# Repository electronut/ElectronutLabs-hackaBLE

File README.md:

> **Note**: This repository has been moved to our GitLab page on May 2019, and will not receive any updates or be monitored. Please follow this link to go to the new repository: https://gitlab.com/electronutlabs-public/ElectronutLabs-HackaBLE

## What is hackaBLE ?

**hackaBLE** is a tiny (~ 18 mm x 28 mm) Open Source Nordic nRF52832 based BLE development board you can embed in your BLE projects. It's designed such that you can use it in three ways:

- On a breadboard
- On a custom PCB, hand-soldered easily using the castellated 2.54 mm pitch headers
- On a custom PCB, using a stencil and oven, making use of extra pads underneath the PCB

hackaBLE uses offers more value than just using the BLE module directly - since it incorporates the necessary passive components - including the ones for the buck converter for power saving - and adds an RGB LED and a button for convenience. It's also much easier to solder than the bare modules. 

**Features**

- Raytac MDBT42 based on Nordic Semiconductor's nRF52832 SOC with chip antenna
- RGB LED
- Button user configurable, set as RESET by default
- SWD programming headers
- MCP1702 3.3 V LDO
- Reverse current protection.

Currently, there are two versions available in the market. Select your version of hackaBLE from below and follow the documentation. 

<h3><a href="#hackaBLE_v0.3">hackaBLE v0.3</a></h3>

<h3><a href="#hackaBLE_v2.2">hackaBLE v2.2</a></h3>

<h2 id="hackaBLE_v0.3"></h2>

## hackaBLE v0.3

This is the latest version of hackaBLE it uses **Raytac's nRF52832 module** by Nordic Semiconductors. This version uses MCP1702, a 3.3 V voltage and protection diode at the input which enables hackaBLE to consume very low current and also provides reverse current protection. It also comes with an RGB LED, user reset button and SWD programming headers.  

### hackaBLE v0.3 pinout

### hackaBLE v0.3 PCB Footprint

### hackaBLE v0.3 Schematic and Datasheet

- [schematic](pcb/ver0.3/hackaBLE_Schematic.pdf)
- datasheet

<hr>
<h2 id="hackaBLE_v2.2"></h2>

## hackaBLE v2.2

hackaBLE v2.2 is a redesigned hackaBLE that used the BLE SoC directly rather than a module. This version of hackaBLE also comes with an RGB LED, button, and SWD programming headers. It has onboard BLE antenna. 

**[CAUTION]** hackaBLE v2.2 does not come with a regulator since it's designed for low power applications. MAX input to VDD is 3.6 V.

### hackaBLE v2.2 pinout

### Schematic for hackaBLE v2.2

- [Schematic](pcb/ver2.2/hackaBLE.pdf)

## Programming hackaBLE

hackaBLE uses the Nordic nRF52832 which in turn is based on an ARM Cortex-M4 core. So you can really program it with any ARM compatible programmer. We do have a convenient solution though, in the form of our [Bumpy][3] Blackmagic probe compatible SWD debugger and our [PogoProg][4].

As shown above, use the four SWD pins of PogoProg on hackaBLE to upload or debug hackaBLE.

Please [read the bumpy documentation][3] on using Bumpy to program hackaBLE.

For more details on nRF52 programming, please read our guide on [getting started with Nordic nRF5 SDK][1]. 

### Program using Arduino IDE

hackable does not ship with a bootloader, but it is supported in Arduino. Please visit [here](https://github.com/electronut/ElectronutLabs-bluey#Arduino) for details (but select Hackable in the board's menu).

[Here's](https://electronut.in/using-hackable-with-arduino/) a blog article which will help you create a BLE custom characteristic and program it to hackaBLE using Arduino IDE.

For more detailed programming guide go [here](https://docs.electronut.in/hackaBLE/programming_guide/)

## Soldering headers hackaBLE

hackaBLE can be used on a breadboard. Here's a video that shows how to solder headers on to hackaBLE.

## Buy a hackaBLE!

hackaBLE is available for purchase from our [Tindie store][2]. Please email us at **info@electronut.in** if you have any questions.

[1]: https://github.com/electronut/ElectronutLabs-bluey/blob/master/nrf5-sdk-setup.md
[2]: https://www.tindie.com/stores/ElectronutLabs/
[3]: https://gitlab.com/electronut/ElectronutLabs-Bumpy
[4]: https://gitlab.com/electronutlabs-public/ElectronutLabs-PogoProg

## Code Repository

You can find all code and design files related to HackaBLE in this [repository](https://gitlab.com/electronutlabs-public/ElectronutLabs-HackaBLE).

## About Electronut Labs

**Electronut Labs** is an Embedded Systems company based in Bangalore, India. More 
information at our [website](https://electronut.in).

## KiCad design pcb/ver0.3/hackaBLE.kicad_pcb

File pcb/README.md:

# BlueyCore
A compact Nordic nRF52832 BLE module for embedding in projects.

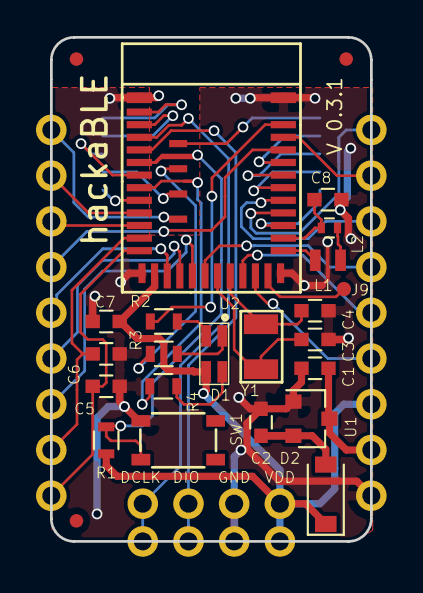
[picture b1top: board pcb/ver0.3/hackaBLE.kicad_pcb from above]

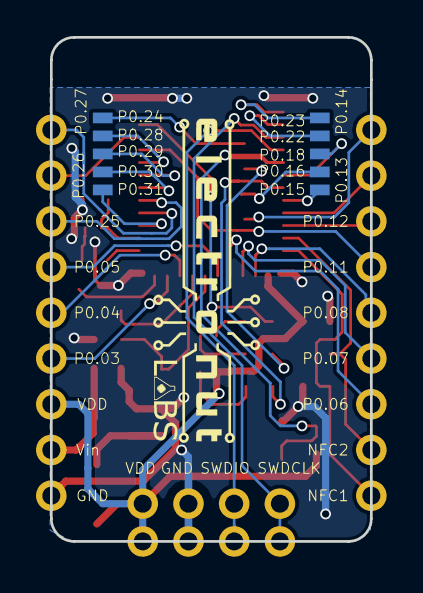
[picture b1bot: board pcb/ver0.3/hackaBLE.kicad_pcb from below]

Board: 2 copper layers, 17.8 x 28.0 mm, 29 parts (2 on the bottom side), 44 nets.

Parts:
C1, C2, C8: 1uF; C_0603
C3, C4: 12pF; C_0603
C5, C6: 300pF; C_0603
C7: 10uF; C_0603
D1: LED_ARGB; RGB_LED
D2: MBR130; D_SOD-123
J1: INPUT; Pin_Header_Straight_1x02_Pitch2.54
J2: NFC; Pin_Header_Straight_1x02_Pitch2.54
J3, J8: SWD; Pin_Header_Straight_1x04_Pitch2.54
J4, J6: GPIO; Pin_Header_Straight_1x07_Pitch2.54
J5, J7: GPIO; 5pin_header
J9: TEST_1P; test_point
L1: 10uH; Neosid_Inductor_SM0603CG
L2: 15nH; L_0402
R1: 10K; R_0603
R2: 200R; R_0603
R3, R4: 100R; R_0603
SW1: SW_Push; PTS810_Switch
U1: MCP1702; SOT-23
U2: MDBT42
Y1: 32.768KHz; ABS07_crystal

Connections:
BLUE: R4.2, U2.8
GND: C1.1, C2.1, C3.2, C4.2, C5.2, C6.1, C7.1, C8.2, J1.2, J3.3, J8.3, SW1.1, U1.1, U2.1, U2.14, U2.25, U2.37
GREEN: R3.2, U2.39
NFC1: C5.1, J2.1, U2.13
NFC2: C6.2, J2.2, U2.12
unnamed: C2.2, D2.2, U1.2
unnamed: C3.1, U2.20, Y1.1
unnamed: C4.1, U2.21, Y1.2
unnamed: C8.1, L2.1, U2.27
unnamed: D1.1, R3.1
unnamed: D1.2, R2.1
unnamed: D1.4, R4.1
unnamed: L1.1, L2.2
unnamed: L1.2, U2.26
P0.02: J9.1, U2.24
P0.03: J6.2, U2.23
P0.04: J6.3, U2.22
P0.05: J6.4, U2.19
P0.06: J4.1, U2.18
P0.07: J4.2, U2.17
P0.08: J4.3, U2.16
P0.11: J4.4, U2.34
P0.12: J4.5, U2.11
P0.13: J4.6, U2.10
P0.14: J4.7, U2.41
P0.15: J5.1, U2.9
P0.16: J5.2, U2.40
P0.18: J5.3, U2.7
P0.22: J5.4, U2.3
P0.23: J5.5, U2.2
P0.24: J7.1, U2.38
P0.25: J6.5, U2.30
P0.26: J6.6, U2.35
P0.27: J6.7, U2.29
P0.28: J7.2, U2.33
P0.29: J7.3, U2.32
P0.30: J7.4, U2.31
P0.31: J7.5, U2.28
RED: R2.2, U2.36
RESET: R1.2, SW1.2, U2.6
SWDCLK: J3.1, J8.1, U2.4
SWDIO: J3.2, J8.2, U2.5
VDD: C7.2, D1.3, D2.1, J3.4, J6.1, J8.4, R1.1, U2.15
Vin: C1.2, J1.1, U1.3

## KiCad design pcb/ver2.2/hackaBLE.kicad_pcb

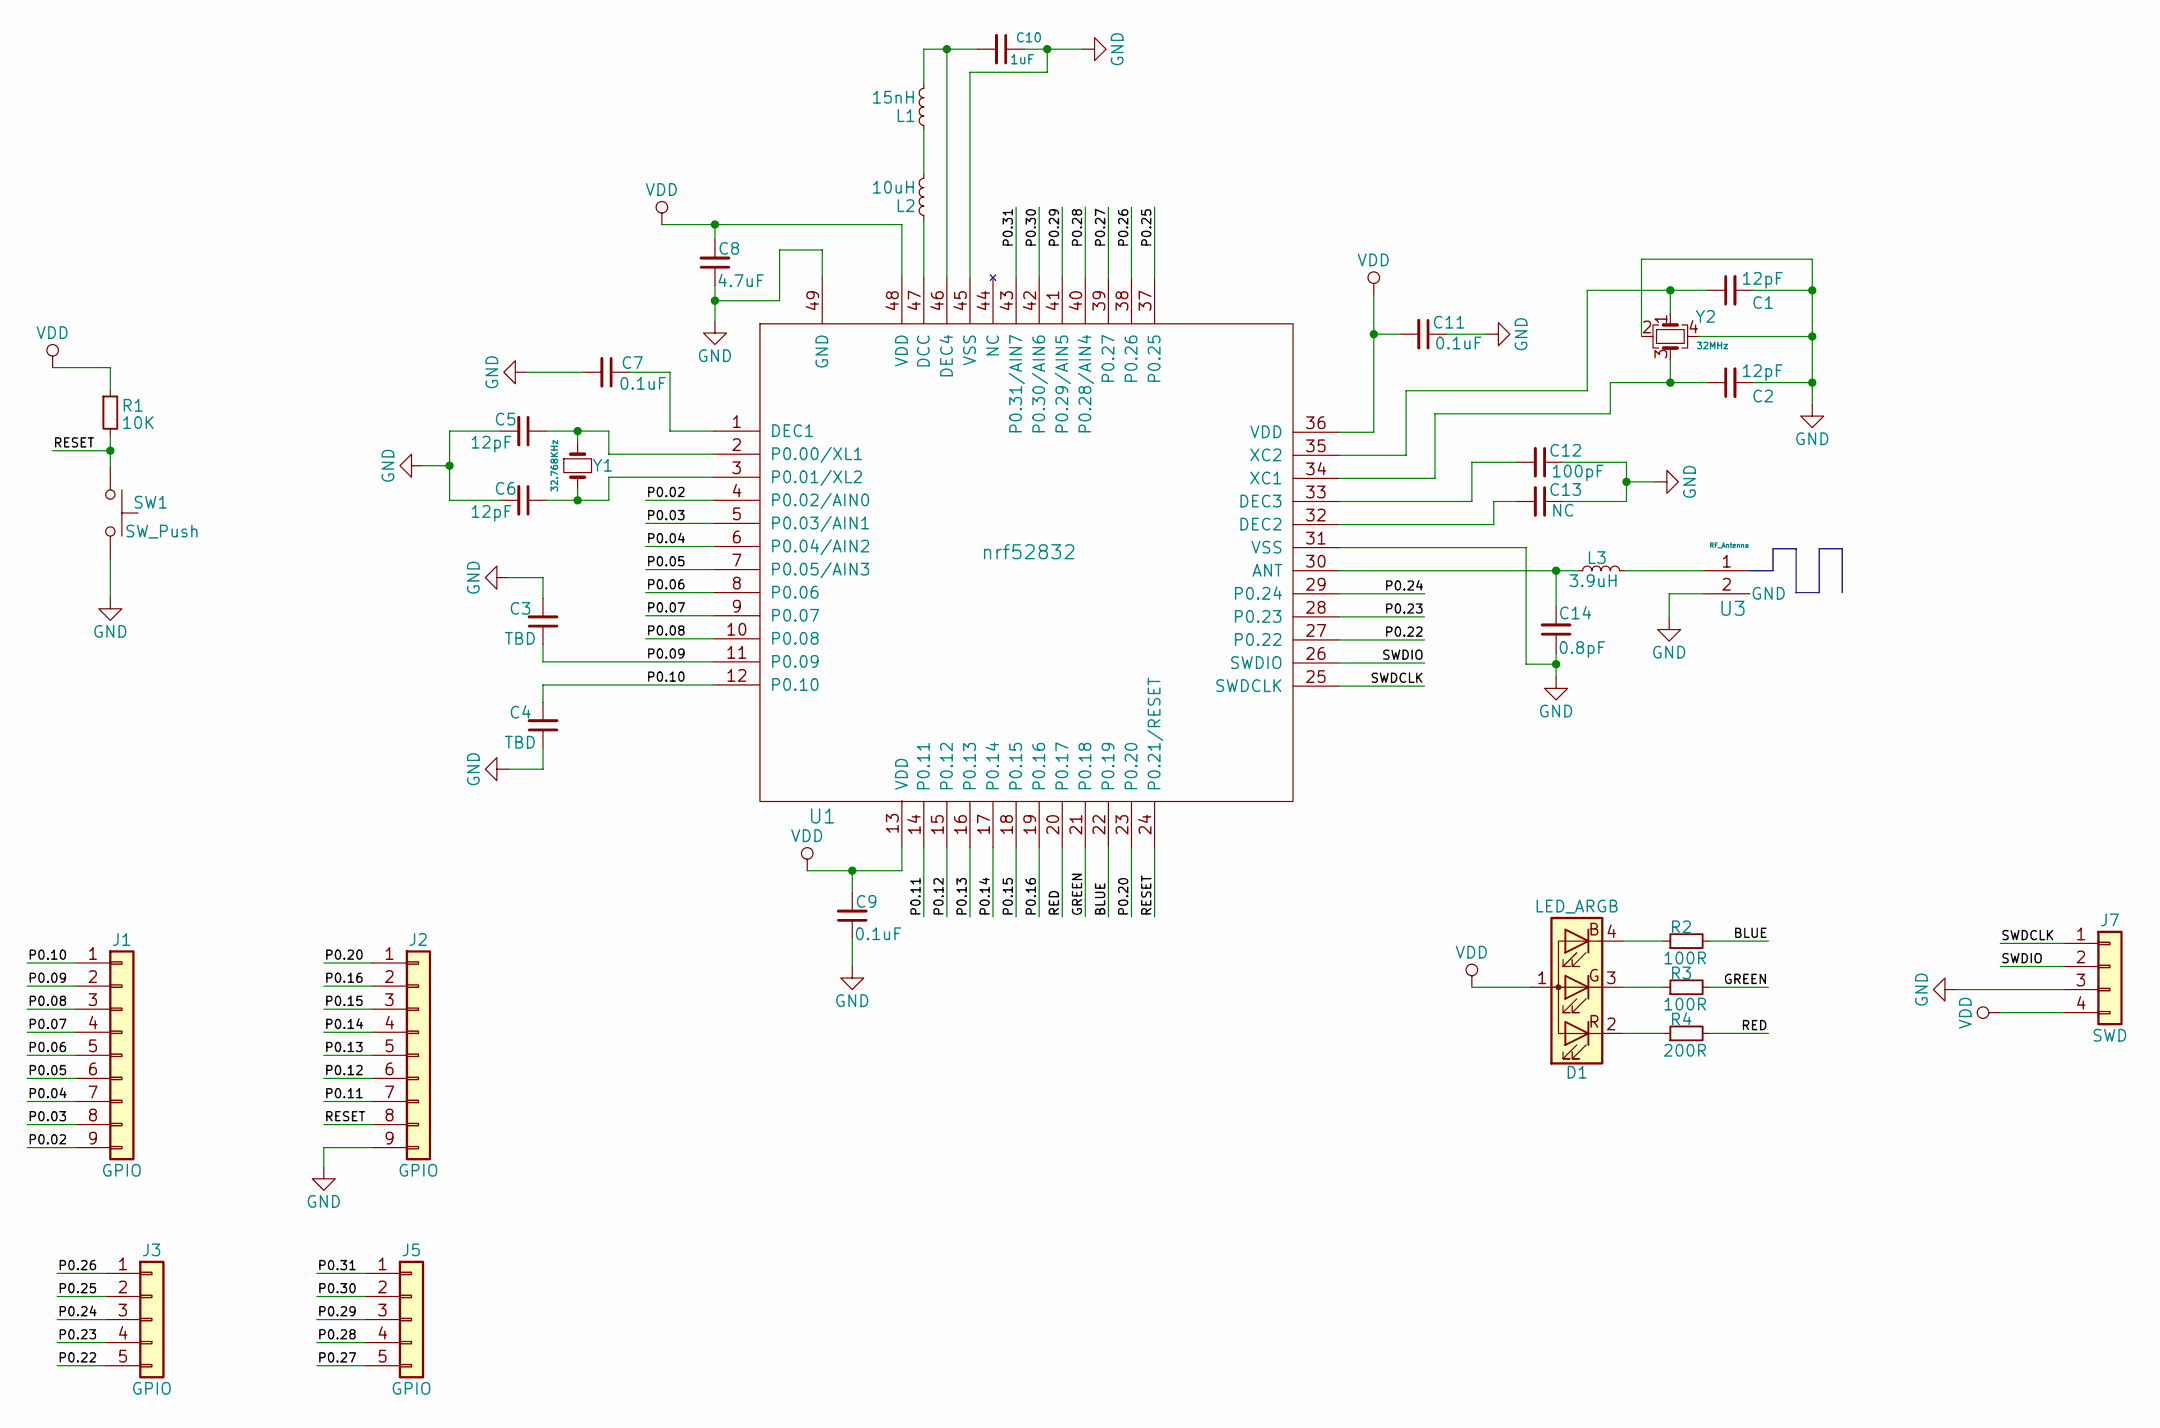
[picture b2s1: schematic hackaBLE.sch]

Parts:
C1, C2, C5, C6: 12pF; C_0402
C3, C4: TBD; C_0603
C7, C9, C11: 0.1uF; C_0402
C8: 4.7uF; C_0603
C10: 1uF; C_0603
C12: 100pF; C_0402
C13: NC; C_0402
C14: 0.8pF; SMD_0402
D1: LED_ARGB; RGB_LED
J1, J2: GPIO; PinHeaderStraight1x09_Pitch2.54mm
J3, J5: GPIO; 5pin_header
J7: SWD; Pin_Header_Straight_1x05_Pitch2.54mm
L1: 15nH; C_0402
L2: 10uH; Neosid_Inductor_SM0603CG
L3: 3.9uH; SMD_0402
R1: 10K; R_0603
R2, R3: 100R; R_0603
R4: 200R; R_0603
SW1: SW_Push; PTS810_Switch
U1: nrf52832; nRF52832
U3: RF_Antenna; Antenna-2.45GHZ_mirror
Y1: 32.768KHz; ABS07_crystal
Y2: 32MHz; 32MHz_crystal

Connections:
/BLUE: R2.2, U1.22 (P0.19)
/GREEN: R3.2, U1.21 (P0.18)
/P0.02: J1.9, U1.4 (P0.02/AIN0)
/P0.03: J1.8, U1.5 (P0.03/AIN1)
/P0.04: J1.7, U1.6 (P0.04/AIN2)
/P0.05: J1.6, U1.7 (P0.05/AIN3)
/P0.06: J1.5, U1.8 (P0.06)
/P0.07: J1.4, U1.9 (P0.07)
/P0.08: J1.3, U1.10 (P0.08)
/P0.09: C3.1, J1.2, U1.11 (P0.09)
/P0.10: C4.2, J1.1, U1.12 (P0.10)
/P0.11: J2.7, U1.14 (P0.11)
/P0.12: J2.6, U1.15 (P0.12)
/P0.13: J2.5, U1.16 (P0.13)
/P0.14: J2.4, U1.17 (P0.14)
/P0.15: J2.3, U1.18 (P0.15)
/P0.16: J2.2, U1.19 (P0.16)
/P0.20: J2.1, U1.23 (P0.20)
/P0.22: J3.5, U1.27 (P0.22)
/P0.23: J3.4, U1.28 (P0.23)
/P0.24: J3.3, U1.29 (P0.24)
/P0.25: J3.2, U1.37 (P0.25)
/P0.26: J3.1, U1.38 (P0.26)
/P0.27: J5.5, U1.39 (P0.27)
/P0.28: J5.4, U1.40 (P0.28/AIN4)
/P0.29: J5.3, U1.41 (P0.29/AIN5)
/P0.30: J5.2, U1.42 (P0.30/AIN6)
/P0.31: J5.1, U1.43 (P0.31/AIN7)
/RED: R4.2, U1.20 (P0.17)
/RESET: J2.8, R1.2, SW1.1, U1.24 (P0.21/RESET)
/SWDCLK: J7.1, U1.25 (SWDCLK)
/SWDIO: J7.2, U1.26 (SWDIO)
GND: C1.2, C2.2, C3.2, C4.1, C5.2, C6.2, C7.2, C8.1, C9.1, C10.1, C11.1, C12.1, C13.1, C14.1, J2.9, J7.3, SW1.2, U1.31 (VSS), U1.45 (VSS), U1.49 (GND), U3.2 (GND), Y2.2, Y2.4
unnamed: C1.1, U1.35 (XC2), Y2.1
unnamed: C2.1, U1.34 (XC1), Y2.3
unnamed: C5.1, U1.2 (P0.00/XL1), Y1.1
unnamed: C6.1, U1.3 (P0.01/XL2), Y1.2
unnamed: C7.1, U1.1 (DEC1)
unnamed: C10.2, L1.2, U1.46 (DEC4)
unnamed: C12.2, U1.33 (DEC3)
unnamed: C13.2, U1.32 (DEC2)
unnamed: C14.2, L3.1, U1.30 (ANT)
unnamed: D1.2 (RK), R4.1
unnamed: D1.3 (GK), R3.1
unnamed: D1.4 (BK), R2.1
unnamed: L1.1, L2.2
unnamed: L2.1, U1.47 (DCC)
unnamed: L3.2, U3.1
VDD: C8.2, C9.2, C11.2, D1.1 (A), J7.4, R1.1, U1.13 (VDD), U1.36 (VDD), U1.48 (VDD)

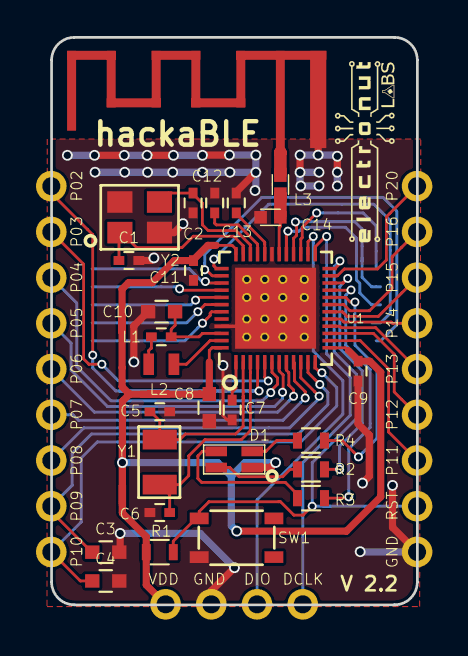
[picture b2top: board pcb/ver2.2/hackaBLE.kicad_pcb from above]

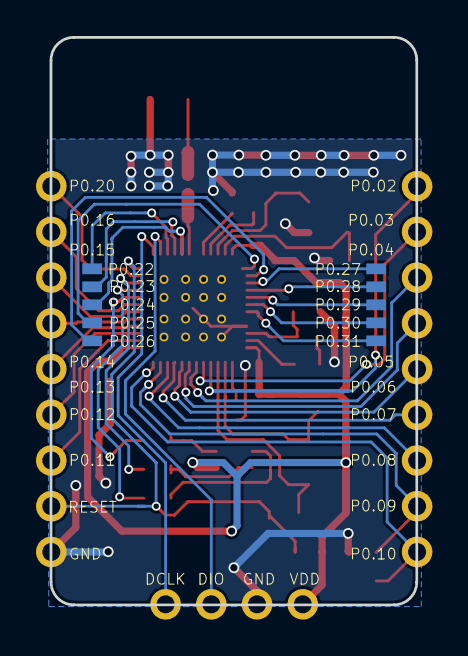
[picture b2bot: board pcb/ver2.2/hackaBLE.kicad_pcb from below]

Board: 2 copper layers, 20.3 x 31.5 mm, 32 parts (2 on the bottom side), 49 nets.

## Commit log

2017-11-16 added schematic
2018-06-09 Air quality monitor code
2018-06-09 Create Python_script
2018-06-09 files upadate
2018-07-17 Add arduino setup details
2018-08-27 Deployed b1161c8 with MkDocs version: 0.16.3
2018-08-27 switch to mkdocs
2018-12-14 ver2.2 pcb files are updated
2018-12-17 epaper demo added
2018-12-17 epaper demo working
2018-12-17 updated hackable2
2018-12-20 photo fixed
2018-12-20 footprint added
2018-12-21 updated epaper code
2018-12-22 epaper image transfer implementation
2019-01-24 Update index.md
    updated links toimages
2019-04-23 added hackable v0.3
2019-04-25 added features and refined details
2019-04-25 ver0.3 pcb files added
2019-04-25 reorder
2019-04-25 Add programming guide.
2019-04-29 code cleanup
2019-04-29 scripts for image data transfer
2019-04-29 Environmental Sensing service with bme280 sensor
2019-04-29 formatting
2019-04-29 readme
2019-04-29 doc update
2019-04-30 added web bluetooth support to hackable temp and humidity data
2019-04-30 fixed index file path
2019-04-30 fixed typo and spacing on programming guide
2019-04-30 fixed typo
2019-05-14 links to gitlab, an remove old files.
2019-05-16 fix link
2019-05-16 Fix link.
2019-05-16 moved to gitlab
